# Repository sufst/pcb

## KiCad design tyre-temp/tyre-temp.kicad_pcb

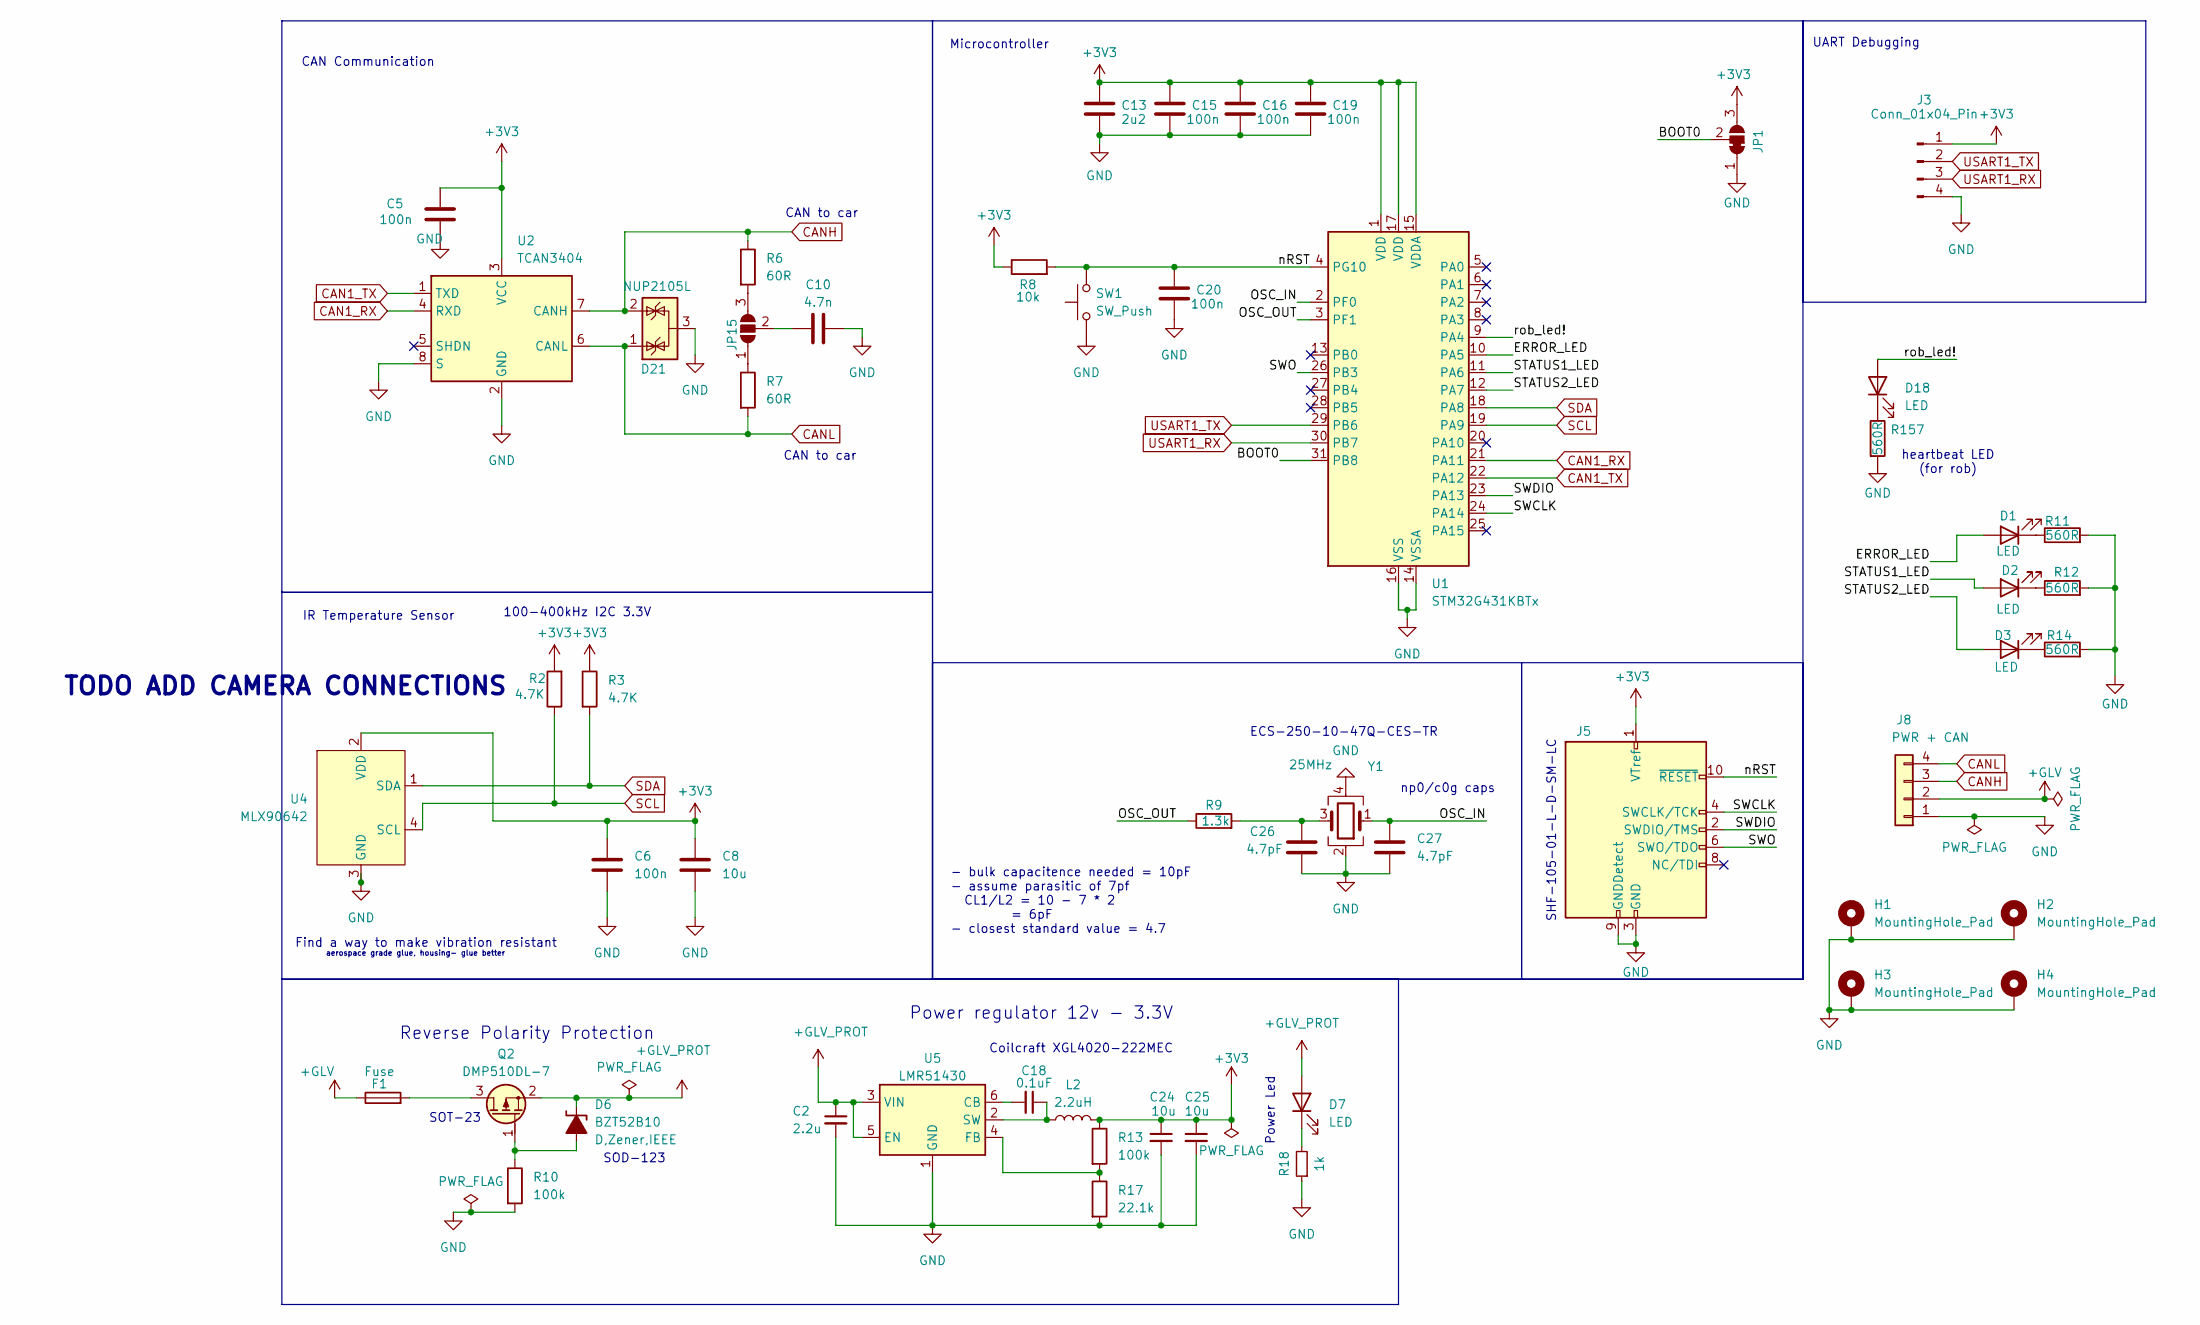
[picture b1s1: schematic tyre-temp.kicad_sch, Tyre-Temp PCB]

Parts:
C2: 2.2u; C_0603_1608Metric_Pad1.08x0.95mm_HandSolder
C5, C6, C15, C16, C19, C20: 100n; C_0603_1608Metric_Pad1.08x0.95mm_HandSolder
C8, C24, C25: 10u; C_0805_2012Metric_Pad1.18x1.45mm_HandSolder
C10: 4.7n; C_0603_1608Metric_Pad1.08x0.95mm_HandSolder
C13: 2u2; C_0603_1608Metric_Pad1.08x0.95mm_HandSolder
C18: 0.1uF; C_0603_1608Metric_Pad1.08x0.95mm_HandSolder
C26, C27: 4.7pF; C_0603_1608Metric_Pad1.08x0.95mm_HandSolder; Mouser Order Number 791-0402N4R7C500CT
D1, D2, D3, D7, D18: LED; LED_0603_1608Metric_Pad1.05x0.95mm_HandSolder
D6: BZT52B10; D_SOD-123; MPN BZT52B10
D21: NUP2105L; SOT-23; Mouser Order Number 863-NUP2105LT1G
F1: Fuse; Fuse_0603_1608Metric_Pad1.05x0.95mm_HandSolder
H1, H2, H3, H4: MountingHole_Pad; MountingHole_3.2mm_M3_ISO7380_Pad_TopBottom
J3: Conn_01x04_Pin; PinHeader_1x04_P2.54mm_Vertical
J5: SHF10501LDSMLC; Mouser Order Number 200-SHF10501LDSMLC
J8: PWR + CAN; Molex_Micro-Fit_3.0_43045-0400_2x02_P3.00mm_Horizontal
JP1: SolderJumper_3_Bridged12; SolderJumper-3_P1.3mm_Bridged2Bar12_RoundedPad1.0x1.5mm
JP15: SolderJumper_3_Open; SolderJumper-3_P1.3mm_Open_RoundedPad1.0x1.5mm
L2: 2.2uH; L_Coilcraft_XAL4020-XXX; MPN XAL4020-222MEC
Q2: DMP510DL-7; SOT-23
R2, R3: 4.7K; R_0603_1608Metric_Pad0.98x0.95mm_HandSolder
R6, R7: 60R; R_0603_1608Metric_Pad0.98x0.95mm_HandSolder
R8: 10k; R_0603_1608Metric_Pad0.98x0.95mm_HandSolder
R9: 1.3k; R_0603_1608Metric_Pad0.98x0.95mm_HandSolder; Mouser Order Number 603-RC0402FR-071K3L
R10, R13: 100k; R_0603_1608Metric_Pad0.98x0.95mm_HandSolder
R11, R12, R14, R157: 560R; R_0603_1608Metric_Pad0.98x0.95mm_HandSolder; Mouser Order Number 603-RC0402FR-07560RL
R17: 22.1k; R_0603_1608Metric_Pad0.98x0.95mm_HandSolder
R18: 1k; R_0603_1608Metric_Pad0.98x0.95mm_HandSolder
SW1: SW_Push; SW_Push_1P1T_NO_CK_KMR2
U1: STM32G431KBTx; LQFP-32_7x7mm_P0.8mm
U2: TCAN3404; TSOT-23-8_HandSoldering
U4: MLX90642
U5: LMR51430; SOT-23-6; MPN LMR51430YDDCR
Y1: 25MHz; Resonator_SMD_ECS_ECX-1247Q_1.6x1.2x0.3mm; Mouser Order Number 520-250-10-47Q-CEST

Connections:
+3V3: C5.1, C6.1, C8.1, C13.2, C15.2, C16.2, C19.2, C24.1, C25.1, J3.1, J5.1 (VTref), JP1.3 (B), L2.2, R2.2, R3.1, R8.1, R13.1, U1.1 (VDD), U1.15 (VDDA), U1.17 (VDD), U2.3 (VCC), U4.2 (VDD)
+GLV: F1.1, J8.2
+GLV_PROT: C2.1, D6.1 (K-), D7.2 (A), Q2.2 (S), U5.3 (VIN), U5.5 (EN)
/BOOT0: JP1.2 (C), U1.31 (PB8)
/ERROR_LED: D1.2 (A), U1.10 (PA5)
/OSC_IN: C27.1, U1.2 (PF0), Y1.1
/OSC_OUT: R9.1, U1.3 (PF1)
/STATUS1_LED: D2.2 (A), U1.11 (PA6)
/STATUS2_LED: D3.2 (A), U1.12 (PA7)
/SWCLK: J5.4 (SWCLK/TCK), U1.24 (PA14)
/SWDIO: J5.2 (SWDIO/TMS), U1.23 (PA13)
/SWO: J5.6 (SWO/TDO), U1.26 (PB3)
/nRST: C20.2, J5.10 (~RESET), R8.2, SW1.2, U1.4 (PG10)
/rob_led!: D18.2 (A), U1.9 (PA4)
CAN1_RX: U1.21 (PA11), U2.4 (RXD)
CAN1_TX: U1.22 (PA12), U2.1 (TXD)
CANH: D21.2 (K), J8.3, R6.1, U2.7 (CANH)
CANL: D21.1 (K), J8.4, R7.2, U2.6 (CANL)
GND: C2.2, C5.2, C6.2, C8.2, C10.2, C13.1, C15.1, C16.1, C19.1, C20.1, C24.2, C25.2, C26.2, C27.2, D21.3 (A), H1.1, H2.1, H3.1, H4.1, J3.4, J5.3 (GND), J5.5 (GND), J5.9 (GNDDetect), J8.1, JP1.1 (A), R10.2, R11.2, R12.2, R14.2, R17.2, R18.1, R157.2, SW1.1, U1.14 (VSSA), U1.16 (VSS), U1.32 (VSS), U2.2 (GND), U2.8 (S), U4.3 (GND), U5.1 (GND), Y1.2, Y1.4
unnamed: C26.1, R9.2, Y1.3
unnamed: D1.1 (K), R11.1
unnamed: D2.1 (K), R12.1
unnamed: D3.1 (K), R14.1
unnamed: D6.2 (A+), Q2.1 (G), R10.1
unnamed: D7.1 (K), R18.2
unnamed: D18.1 (K), R157.1
unnamed: JP15.1 (A), R7.1
unnamed: JP15.3 (B), R6.2
unnamed: C10.1, JP15.2 (C)
unnamed: F1.2, Q2.3 (D)
unnamed: C18.2, U5.6 (CB)
unnamed: R13.2, R17.1, U5.4 (FB)
unnamed: C18.1, L2.1, U5.2 (SW)
SCL: R2.1, U1.19 (PA9), U4.4 (SCL)
SDA: R3.2, U1.18 (PA8), U4.1 (SDA)
USART1_RX: J3.3, U1.30 (PB7)
USART1_TX: J3.2, U1.29 (PB6)

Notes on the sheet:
TODO ADD CAMERA CONNECTIONS
100-400kHz I2C 3.3V
CAN Communication
aerospace grade glue, housing- glue better
Microcontroller
Power regulator 12v - 3.3V
Power Led
CAN to car
Reverse Polarity Protection
Find a way to make vibration resistant
ECS-250-10-47Q-CES-TR
np0/c0g caps
heartbeat LED (for rob)
- bulk capacitence needed = 10pF - assume parasitic of 7pf CL1/L2 = 10 - 7 * 2 = 6pF - closest standard value = 4.7
SHF-105-01-L-D-SM-LC
SOD-123
Coilcraft XGL4020-222MEC
SOT-23
UART Debugging
IR Temperature Sensor

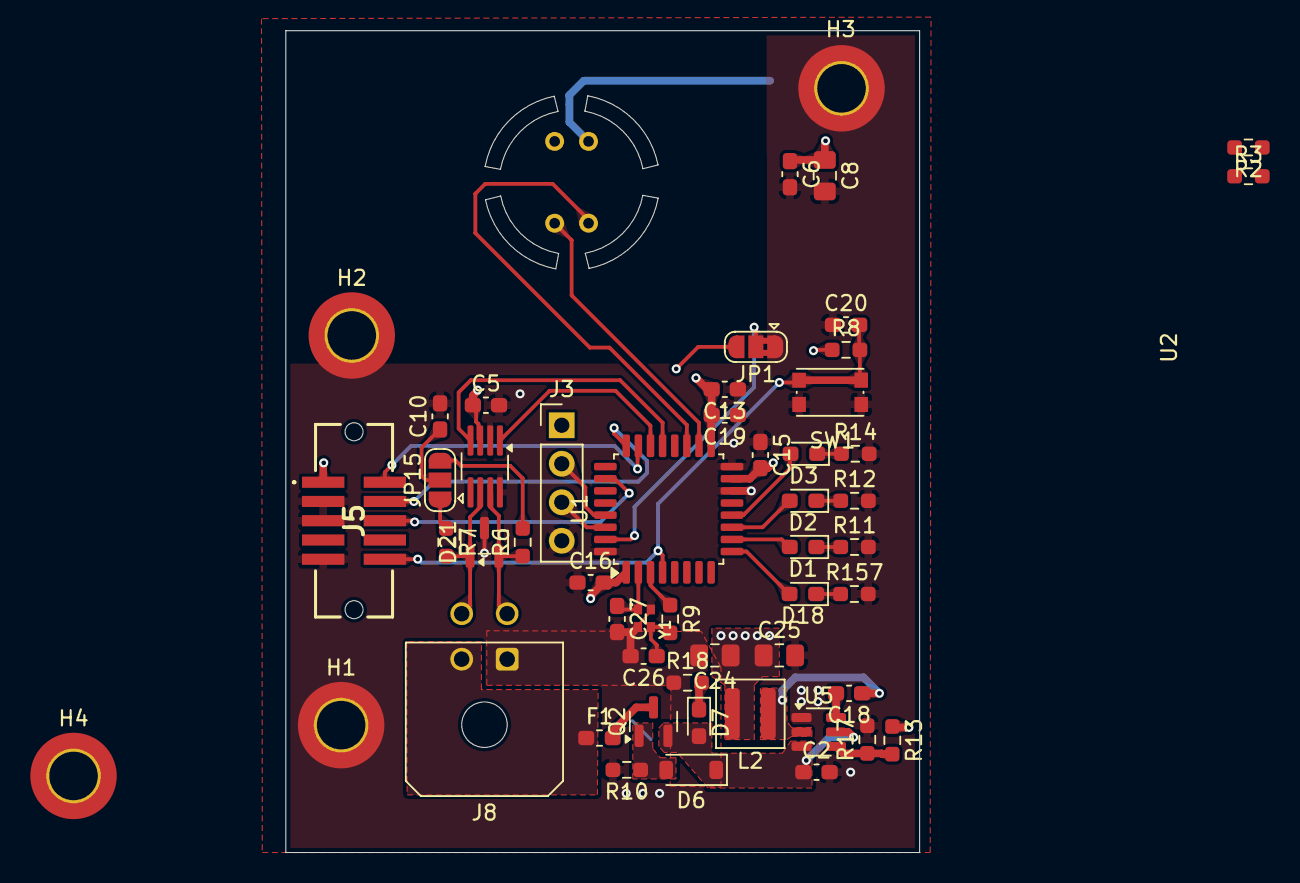
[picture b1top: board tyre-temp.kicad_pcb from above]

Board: 4 copper layers, 41.8 x 54.2 mm, 54 parts (1 on the bottom side), 37 nets.

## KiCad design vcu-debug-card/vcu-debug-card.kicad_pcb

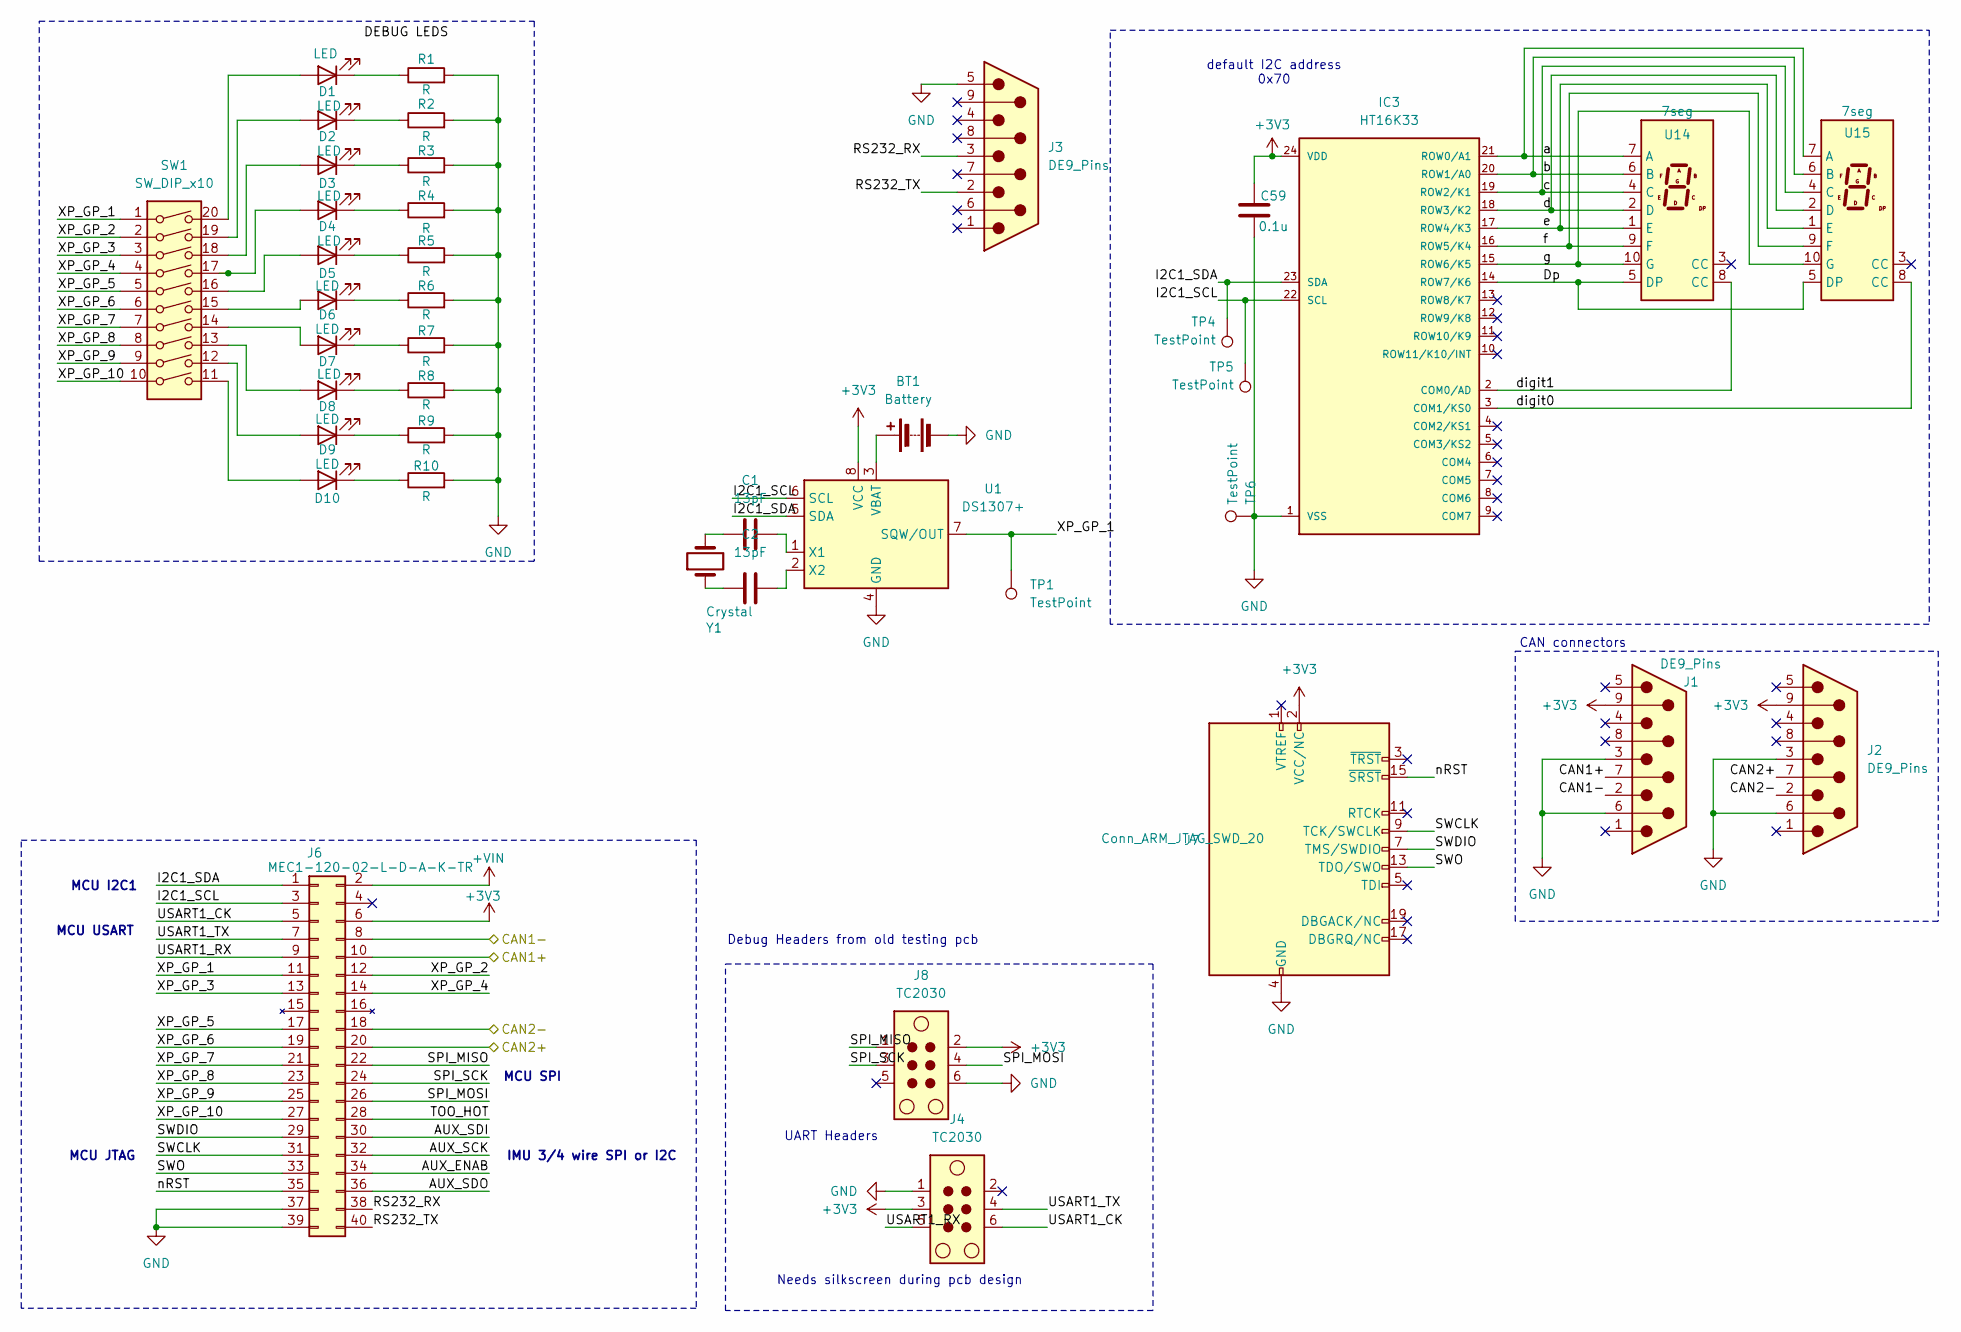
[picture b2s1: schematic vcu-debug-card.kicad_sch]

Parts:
BT1: Battery; BatteryHolder_Multicomp_BC-2001_1x2032; MPN 2898
C1, C2: 13pF; C_0402_1005Metric_Pad0.74x0.62mm_HandSolder; MPN 04023K130FBSTR
C59: 0.1u; C_0805_2012Metric_Pad1.18x1.45mm_HandSolder
D1, D2, D3, D4, D5, D6, D7, D8, D9, D10: LED; LED_0805_2012Metric_Pad1.15x1.40mm_HandSolder
IC3: HT16K33
J1, J2, J3: DE9_Pins; AMPHENOL_D09P71S6GA12LF
J4, J8: TC2030; Tag-Connect_TC2030-IDC-NL_2x03_P1.27mm_Vertical
J6: MEC1-120-02-L-D-A-K-TR; Edge Connector; Mouser Order Number 200-MEC112002LDAKTR
J7: Conn_ARM_JTAG_SWD_20; IDC-Header_2x10_P2.54mm_Vertical
R1, R2, R3, R4, R5, R6, R7, R8, R9, R10: R; R_0603_1608Metric_Pad0.98x0.95mm_HandSolder
SW1: SW_DIP_x10; DipSwitch; MPN NDS10V
TP1, TP4, TP5, TP6: TestPoint; TestPoint_THTPad_D2.5mm_Drill1.2mm
U1: DS1307+; DIP-8_W7.62mm; MPN DS1343E-33+
U14, U15: 7seg; Vishay TDSG5160-MN 7-Segment Display; MPN TDSG5160-MN
Y1: Crystal; CC7V-T1A-32.768kHz-12.5pF-20PPM-TA-QC; MPN CC7V-T1A-32.768kHz-12.5pF-20PPM-TA-QC

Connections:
+3V3: C59.1, IC3.24 (VDD), J1.9, J2.9, J4.3, J6.6, J7.2 (VCC/NC), J8.2, U1.8 (VCC)
+VIN: J6.2
/<NO NET>: J1.2, J6.8
/AUX_ENAB: J6.34
/AUX_SCK: J6.32
/AUX_SDI: J6.30
/AUX_SDO: J6.36
/CAN1+: J1.7, J6.10
/CAN2+: J2.7, J6.20
/CAN2-: J2.2, J6.18
/Dp: IC3.14 (ROW7/K6), U14.5 (DP), U15.5 (DP)
/I2C1_SCL: IC3.22 (SCL), J6.3, TP5.1, U1.6 (SCL)
/I2C1_SDA: IC3.23 (SDA), J6.1, TP4.1, U1.5 (SDA)
/RS232_RX: J3.3, J6.38
/RS232_TX: J3.2, J6.40
/SPI_MISO: J6.22, J8.1
/SPI_MOSI: J6.26, J8.4
/SPI_SCK: J6.24, J8.3
/SWCLK: J6.31, J7.9 (TCK/SWCLK)
/SWDIO: J6.29, J7.7 (TMS/SWDIO)
/SWO: J6.33, J7.13 (TDO/SWO)
/TOO_HOT: J6.28
/USART1_CK: J4.6, J6.5
/USART1_RX: J4.5, J6.9
/USART1_TX: J4.4, J6.7
/XP_GP_1: J6.11, SW1.1, TP1.1, U1.7 (SQW/OUT)
/XP_GP_2: J6.12, SW1.2
/XP_GP_3: J6.13, SW1.3
/XP_GP_4: J6.14, SW1.4
/XP_GP_5: J6.17, SW1.5
/XP_GP_6: J6.19, SW1.6
/XP_GP_7: J6.21, SW1.7
/XP_GP_8: J6.23, SW1.8
/XP_GP_9: J6.25, SW1.9
/XP_GP_10: J6.27, SW1.10
/a: IC3.19 (ROW2/K1), IC3.20 (ROW1/A0), IC3.21 (ROW0/A1), U14.4 (C), U14.6 (B), U14.7 (A), U15.4 (C), U15.6 (B), U15.7 (A)
/d: IC3.18 (ROW3/K2), U14.2 (D), U15.2 (D)
/digit0: IC3.3 (COM1/KS0), U15.8 (CC)
/digit1: IC3.2 (COM0/AD), U14.8 (CC)
/e: IC3.17 (ROW4/K3), U14.1 (E), U15.1 (E)
/f: IC3.16 (ROW5/K4), U14.9 (F), U15.9 (F)
/g: IC3.15 (ROW6/K5), U14.10 (G), U15.10 (G)
/nRST: J6.35, J7.15 (~SRST)
GND: BT1.2 (-), C59.2, IC3.1 (VSS), J1.3, J1.6, J2.3, J2.6, J3.5, J4.1, J6.37, J6.39, J7.4 (GND), J7.6 (GND), J7.8 (GND), J7.10 (GND), J7.12 (GND), J7.14 (GND), J7.16 (GND), J7.18 (GND), J7.20 (GND), J8.6, R1.2, R2.2, R3.2, R4.2, R5.2, R6.2, R7.2, R8.2, R9.2, R10.2, TP6.1, U1.4 (GND)
unnamed: BT1.1 (+), U1.3 (VBAT)
unnamed: C1.1, Y1.2
unnamed: C2.1, Y1.1
unnamed: D1.2 (A), SW1.20
unnamed: D1.1 (K), R1.1
unnamed: D2.2 (A), SW1.19
unnamed: D2.1 (K), R2.1
unnamed: D3.2 (A), SW1.18
unnamed: D3.1 (K), R3.1
unnamed: D4.2 (A), SW1.17
unnamed: D4.1 (K), R4.1
unnamed: D5.2 (A), SW1.16
unnamed: D5.1 (K), R5.1
unnamed: D6.2 (A), SW1.15
unnamed: D6.1 (K), R6.1
unnamed: D7.2 (A), SW1.14
unnamed: D7.1 (K), R7.1
unnamed: D8.2 (A), SW1.13
unnamed: D8.1 (K), R8.1
unnamed: D9.2 (A), SW1.12
unnamed: D9.1 (K), R9.1
unnamed: D10.2 (A), SW1.11
unnamed: D10.1 (K), R10.1
unnamed: C1.2, U1.1 (X1)
unnamed: C2.2, U1.2 (X2)

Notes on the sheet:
MCU SPI
Debug Headers from old testing pcb
Needs silkscreen during pcb design
UART Headers
CAN connectors
MCU I2C1
IMU 3/4 wire SPI or I2C
MCU JTAG
default I2C address 0x70
MCU USART

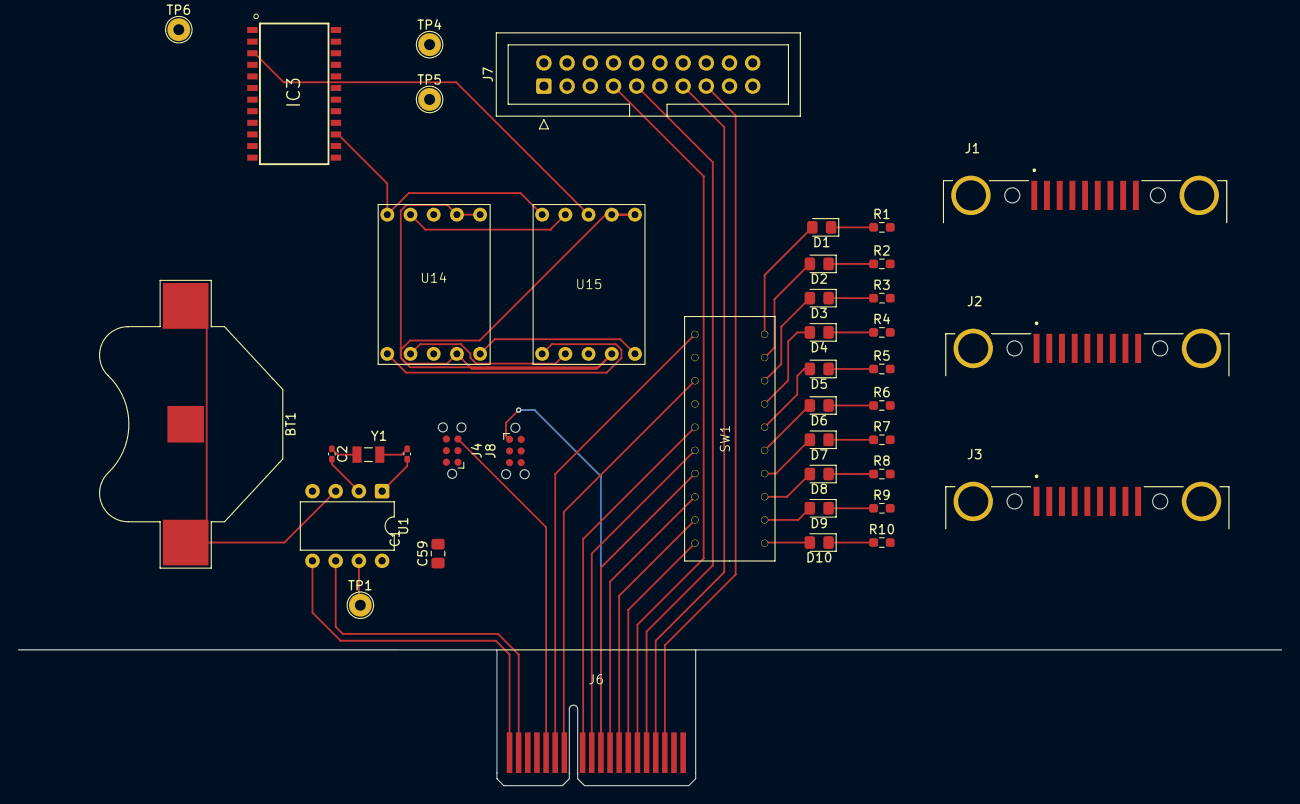
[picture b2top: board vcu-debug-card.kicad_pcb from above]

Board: 4 copper layers, 41 parts (0 on the bottom side), 63 nets.

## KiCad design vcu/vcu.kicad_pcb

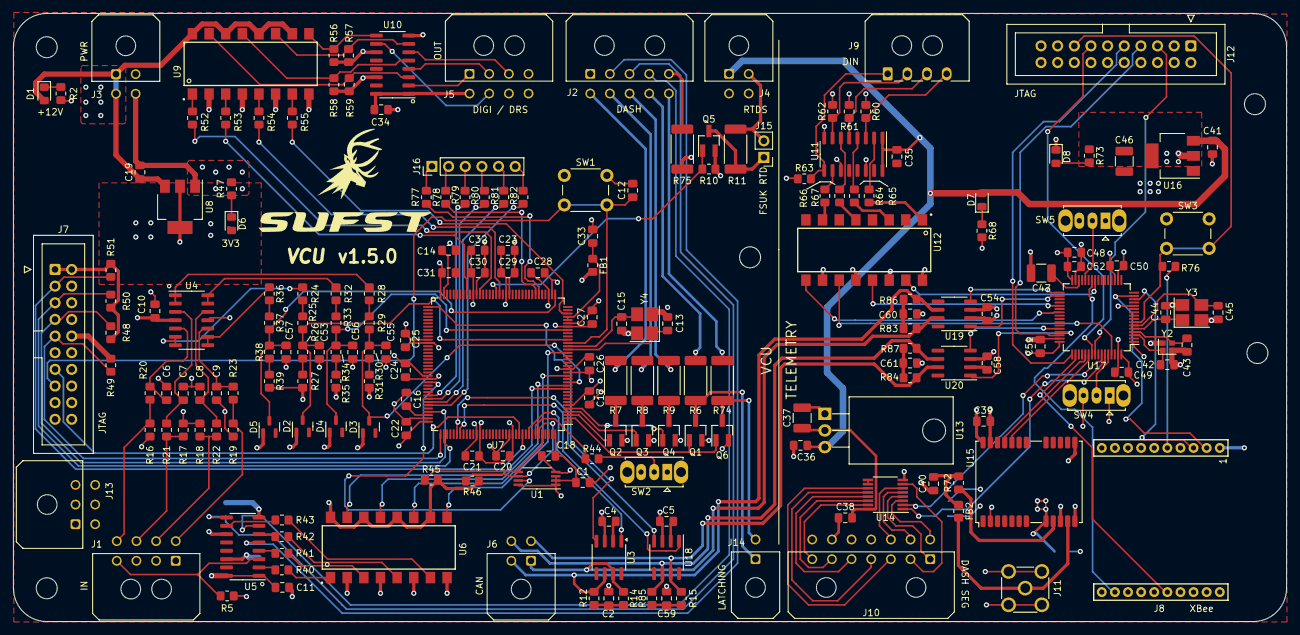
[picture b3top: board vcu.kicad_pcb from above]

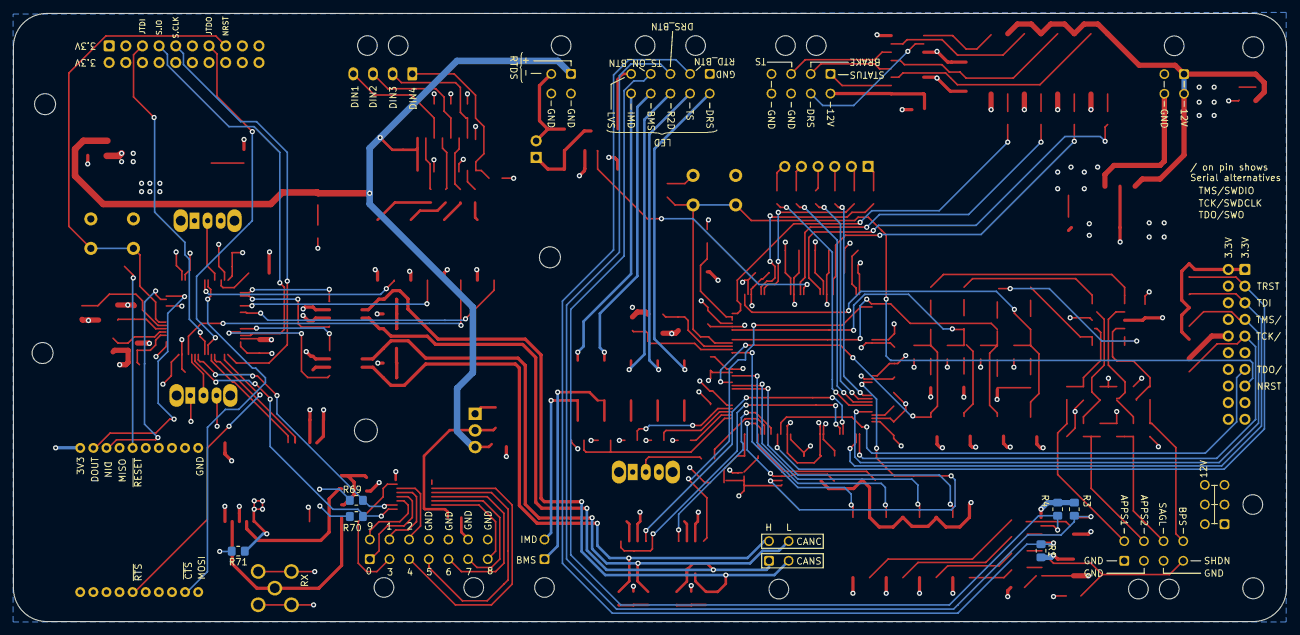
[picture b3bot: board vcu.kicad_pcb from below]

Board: 4 copper layers, 194.3 x 92.8 mm, 210 parts (6 on the bottom side), 177 nets.

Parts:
C1, C4, C5, C6, C7, C8, C9, C10, C11, C12, C17, C18, C19, C20, C21, C22, C24, C25, C26, C27, C28, C29, C30, C33, C34, C35, C36, C38, C54, C58: 100n; C_0805_2012Metric_Pad1.18x1.45mm_HandSolder
C2, C59, C60, C61: 4.7n; C_0805_2012Metric_Pad1.18x1.45mm_HandSolder
C13, C15: 4.3p; C_0805_2012Metric_Pad1.18x1.45mm_HandSolder
C14, C16: 2.2u; C_0805_2012Metric_Pad1.18x1.45mm_HandSolder
C23: 10u; C_0805_2012Metric_Pad1.18x1.45mm_HandSolder
C31: 4.7u; C_0805_2012Metric_Pad1.18x1.45mm_HandSolder
C32: 1u; C_0805_2012Metric_Pad1.18x1.45mm_HandSolder
C37: 10u; C_1210_3225Metric_Pad1.33x2.70mm_HandSolder
C39, C41, C49, C50, C51, C52: 100nF; C_0805_2012Metric_Pad1.18x1.45mm_HandSolder
C40: 47pF; C_0805_2012Metric_Pad1.18x1.45mm_HandSolder
C42, C43: 4p3; C_0805_2012Metric_Pad1.18x1.45mm_HandSolder
C44, C45: 20pF; C_0805_2012Metric_Pad1.18x1.45mm_HandSolder
C46: 10uF; C_1210_3225Metric_Pad1.33x2.70mm_HandSolder
C47: 4u7; C_1210_3225Metric_Pad1.33x2.70mm_HandSolder
C48: 4.7uF; C_0805_2012Metric_Pad1.18x1.45mm_HandSolder
C53, C55, C56, C57: 1n; C_0805_2012Metric_Pad1.18x1.45mm_HandSolder
D1, D6, D7, D8: LED; LED_0805_2012Metric_Pad1.15x1.40mm_HandSolder
D2, D3, D4, D5: BZX84-C3V3; SOT-23
FB1, FB2: 120; R_0805_2012Metric_Pad1.20x1.40mm_HandSolder
H1, H2, H3, H5, H6: M3; MountingHole_3.2mm_M3
J1: IN; Molex_Micro-Fit_3.0_43045-0800_2x04_P3.00mm_Horizontal
J2: DASH CONTROL; Molex_Micro-Fit_3.0_43045-1000_2x05_P3.00mm_Horizontal
J3: PWR; Molex_Micro-Fit_3.0_43045-0400_2x02_P3.00mm_Horizontal
J4: RTDS; Molex_Micro-Fit_3.0_43045-0400_2x02_P3.00mm_Horizontal
J5: OUT; Molex_Micro-Fit_3.0_43045-0800_2x04_P3.00mm_Horizontal
J6: CAN; Molex_Micro-Fit_3.0_43045-0400_2x02_P3.00mm_Horizontal
J7, J12: Conn_ARM_JTAG_SWD_20; IDC-Header_2x10_P2.54mm_Vertical
J8: XBee; XBEE
J9: MCU_DIN; Molex_Micro-Fit_3.0_43650-0400_1x04_P3.00mm_Horizontal
J10: Dash 7 Segment; Molex_Micro-Fit_3.0_43045-1400_2x07_P3.00mm_Horizontal
J11: Conn_Coaxial; SMA_Molex_73251-2200_Horizontal
J13: DASH 12V; Molex_Micro-Fit_3.0_43045-0600_2x03_P3.00mm_Horizontal
J14: BMS+IMD LATCHING; Molex_Micro-Fit_3.0_43045-0200_2x01_P3.00mm_Horizontal
J15: FSUK_RTD; PinHeader_1x02_P2.54mm_Vertical
J16: Spare pins; PinHeader_1x06_P2.54mm_Vertical
Q1, Q2, Q3, Q4, Q5, Q6: FDN359BN; SOT-23_Handsoldering
R1, R3, R4, R5, R44, R45, R46, R48, R49, R50, R51, R56, R57, R58, R59, R60, R61, R62, R63: 10k; R_0805_2012Metric_Pad1.20x1.40mm_HandSolder
R2, R68: 3.3k; R_0805_2012Metric_Pad1.20x1.40mm_HandSolder
R6, R7, R8, R9, R11, R74, R75: 1k; R_2512_6332Metric_Pad1.40x3.35mm_HandSolder
R10: 3k3; R_0805_2012Metric_Pad1.20x1.40mm_HandSolder
R12, R14, R15, R83, R84, R85, R86, R87: 60R; R_0805_2012Metric_Pad1.20x1.40mm_HandSolder
R16, R17, R18, R19: 100k; R_0805_2012Metric_Pad1.20x1.40mm_HandSolder
R20, R21, R22, R23, R40, R41, R42, R43, R64, R65, R66, R67: 1k; R_0805_2012Metric_Pad1.20x1.40mm_HandSolder
R24, R28, R32, R36: 75k; R_0805_2012Metric_Pad1.20x1.40mm_HandSolder
R25, R26, R29, R30, R33, R34, R37, R38: 5.6k; R_0805_2012Metric_Pad1.20x1.40mm_HandSolder
R27, R31, R35, R39: 1.8k; R_0805_2012Metric_Pad1.20x1.40mm_HandSolder
R47, R73: 1k5; R_0805_2012Metric_Pad1.20x1.40mm_HandSolder
R52, R53, R54, R55: 220; R_0805_2012Metric_Pad1.20x1.40mm_HandSolder
R69, R70: 4k7; R_0805_2012Metric_Pad1.20x1.40mm_HandSolder
R71: DNP; R_0805_2012Metric_Pad1.20x1.40mm_HandSolder
R72: 33; R_0805_2012Metric_Pad1.20x1.40mm_HandSolder
R76: 0; R_0805_2012Metric_Pad1.20x1.40mm_HandSolder
R77, R78, R79, R80, R81, R82: 100; R_0805_2012Metric_Pad1.20x1.40mm_HandSolder
SW1, SW3: SW_Push; SW_PUSH_6mm
SW2, SW4, SW5: SW_SPDT; SW_Slide_1P2T_CK_OS102011MS2Q
U1: M24256-DRD; TSSOP-8_4.4x3mm_P0.65mm
U3, U18, U19, U20: MAX3051ESA+; SOIC-8_3.9x4.9mm_P1.27mm
U4: TLV274; SOIC-14_3.9x8.7mm_P1.27mm
U5, U10, U11: HCF4010; SOIC-16_3.9x9.9mm_P1.27mm
U6, U9, U12: ILQ615-4X009T; SOIC254P1005X380-16N
U7: STM32F746ZGT6; LQFP-144_20x20mm_P0.5mm
U8, U16: LD1117S33TR_SOT223; SOT-223-3_TabPin2
U13: LD1117V33; TO-220-3_Horizontal_TabDown
U14: MAX6958BAEE+T; QSOP-16_3.9x4.9mm_P0.635mm
U15: NEO-M9N; ublox_NEO
U17: STM32F446RETx; LQFP-64_10x10mm_P0.5mm
Y2: 32MHz; Crystal_SMD_2016-4Pin_2.0x1.6mm
Y3, Y4: 8MHz; Crystal_SMD_3225-4Pin_3.2x2.5mm_HandSoldering

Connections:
+3.3V: C1.1, C4.2, C5.2, C17.1, C18.1, C20.1, C21.1, C22.1, C23.1, C24.1, C25.1, C26.1, C27.1, C28.1, C29.1, C30.1, C31.1, C32.1, D6.2 (A), FB1.2, J7.1 (VTREF), J7.2 (VCC/NC), R45.2, R46.1, R48.2, R50.2, R51.2, SW2.3 (C), U1.1 (E0), U1.2 (E1), U1.3 (E2), U1.8 (VCC), U3.3 (VDD), U6.10, U6.12, U6.14, U6.16, U7.6 (VBAT), U7.17 (VDD), U7.30 (VDD), U7.39 (VDD), U7.52 (VDD), U7.62 (VDD), U7.72 (VDD), U7.84 (VDD), U7.95 (VDDUSB), U7.108 (VDD), U7.121 (VDD), U7.131 (VDD), U7.144 (VDD), U8.2 (VO), U18.3 (VDD)
+3.3VA: C33.1, FB1.1, U7.32 (VREF+), U7.33 (VDDA)
+3.3VT: C39.2, C46.2, C48.1, C49.1, C50.1, C51.1, C52.1, C54.2, C58.2, J8.1, J12.1 (VTREF), J12.2 (VCC/NC), R69.1, R70.1, R71.1, R73.1, SW4.3 (C), SW5.1 (A), U12.10, U12.12, U12.14, U12.16, U15.2 (D_SEL), U15.8 (~RESET), U15.23 (VCC), U16.2 (VO), U17.1 (VBAT), U17.19 (VDD), U17.32 (VDD), U17.48 (VDD), U17.64 (VDD), U19.3 (VDD), U20.3 (VDD)
+12V: C10.2, C11.2, C19.1, C34.2, C35.2, C36.2, C41.2, D1.2 (A), D7.2 (A), J3.1, J3.3, J4.1, J5.5, J13.1, J13.2, J13.3, J13.4, J13.5, J13.6, U4.4 (V+), U5.1 (VCC), U5.16 (VDD), U8.3 (VI), U9.10, U9.12, U9.14, U9.16, U10.1 (VCC), U10.16 (VDD), U11.1 (VCC), U11.16 (VDD), U13.3 (VI), U16.3 (VI)
/APPS_1_IN: J1.5, R19.1, R23.1
/APPS_2_IN: J1.6, R18.1, R22.1
/BMS_LED: J2.9, R6.1
/BPS_IN: J1.8, R16.1, R20.1
/BRAKE_PRESSED: J5.2, U10.4 (Bout)
/CAN_C_H: J6.3, R15.2, R84.2, U18.7 (CANH), U20.7 (CANH)
/CAN_C_L: J6.4, R85.1, R87.1, U18.6 (CANL), U20.6 (CANL)
/CAN_S_H: J6.1, R14.2, R83.2, U3.7 (CANH), U19.7 (CANH)
/CAN_S_L: J6.2, R12.1, R86.1, U3.6 (CANL), U19.6 (CANL)
/DRS_BTN: J2.3, R3.1, U5.9 (Din)
/DRS_LED: J2.6, R7.1
/DRS_LED_ON: Q2.1 (G), U7.3 (PE4)
/DRS_PWM: J5.6, U10.10 (Dout)
/EEPROM_SCL: R46.2, U1.6 (SCL), U7.139 (PB8)
/EEPROM_SDA: R45.1, U1.5 (SDA), U7.140 (PB9)
/EEPROM_WC: U1.7 (WC), U7.96 (PC6)
/IMD_LED: J2.10, R74.1
/Input Shift/APPS_1_OUT: C57.2, D5.3 (K), R37.2, R38.1, U7.37 (PA3)
/Input Shift/APPS_2_OUT: C56.2, D4.3 (K), R33.2, R34.1, U7.29 (PC3)
/Input Shift/BPS_OUT: C53.2, D2.3 (K), R25.2, R26.1, U7.26 (PC0)
/Input Shift/DOUT_1: U6.15, U7.11 (PF1)
/Input Shift/DOUT_2: U6.13, U7.12 (PF2)
/Input Shift/DOUT_3: U6.11, U7.15 (PF5)
/Input Shift/DOUT_4: U6.9, U7.22 (PF10)
/Input Shift/SAGL_OUT: C55.2, D3.3 (K), R29.2, R30.1, U7.13 (PF3)
/LVS_LED: J2.5, R75.1
/Output Level Shifting/DIN_1: R52.1, U7.60 (PE9)
/Output Level Shifting/DIN_2: R53.1, U7.64 (PE11)
/Output Level Shifting/DIN_3: R54.1, U7.54 (PF14)
/Output Level Shifting/DIN_4: R55.1, U7.34 (PA0)
/R2D_BTN: J2.2, R1.1, U5.5 (Bin)
/R2D_LED: J2.8, R9.1
/R2D_LED_ON: Q4.1 (G), U7.5 (PE6)
/R2D_SIREN_ON: Q5.1 (G), R10.2, U7.55 (PF15)
/RTDS-: J4.2, J15.2, R11.2
/SAGL_IN: J1.7, R17.1, R21.1
/SHDN_STATE: J1.4, R5.1, U5.3 (Ain)
/STATUS: J5.1, U10.2 (Aout)
/STM32-F746ZG/BOOT0: R44.2, U7.138 (BOOT0)
/STM32-F746ZG/CAN1_RX: U7.114 (PD0), U18.4 (RXD)
/STM32-F746ZG/CAN1_TX: U7.115 (PD1), U18.1 (TXD)
/STM32-F746ZG/CAN2_RX: U3.4 (RXD), U7.73 (PB12)
/STM32-F746ZG/CAN2_TX: U3.1 (TXD), U7.136 (PB6)
/STM32-F746ZG/NRST: C12.1, J7.15 (~SRST), SW1.2, U7.25 (NRST)
/STM32-F746ZG/PWR_LED_K: D6.1 (K), R47.1
/STM32-F746ZG/SW_BOOT0: R44.1, SW2.2 (B)
/STM32-F746ZG/TCK/SWDCLK: J7.9 (TCK/SWCLK), R49.2, U7.109 (PA14)
/STM32-F746ZG/TDI: J7.5 (TDI), R50.1, U7.110 (PA15)
/STM32-F746ZG/TDO/SWO: J7.13 (TDO/SWO), U7.133 (PB3)
/STM32-F746ZG/TMS/SWDIO: J7.7 (TMS/SWDIO), R48.1, U7.105 (PA13)
/STM32-F746ZG/TRST: J7.3 (~TRST), R51.1, U7.134 (PB4)
/TS_ON: J5.3, U10.6 (Cout)
/TS_ON_BTN: J2.4, R4.1, U5.7 (Cin)
/TS_ON_LED: J2.7, R8.1
/TS_ON_LED_ON: Q3.1 (G), U7.4 (PE5)
/Telemetry/3V3_LED: C37.1, C38.2, U13.2 (VO), U14.16 (V+)
/Telemetry/CAN1_RX: U17.44 (PA11), U20.4 (RXD)
/Telemetry/CAN1_TX: U17.45 (PA12), U20.1 (TXD)
/Telemetry/CAN2_RX: U17.33 (PB12), U19.4 (RXD)
/Telemetry/CAN2_TX: U17.34 (PB13), U19.1 (TXD)
/Telemetry/GPS/GPS_RX: U15.21 (RXD/SPI_MOSI), U17.53 (PC12)
/Telemetry/GPS/GPS_TX: U15.20 (TXD/SPI_MISO), U17.54 (PD2)
/Telemetry/SEG0: J10.1, U14.4 (DIG0/SEG0)
/Telemetry/SEG1: J10.9, U14.5 (DIG1/SEG1)
/Telemetry/SEG2: J10.10, U14.6 (DIG2/SEG2)
/Telemetry/SEG3: J10.2, U14.7 (DIG3/SEG3)
/Telemetry/SEG4: J10.3, U14.11 (SEG4)
/Telemetry/SEG5: J10.4, U14.12 (SEG5)
/Telemetry/SEG6: J10.5, U14.13 (SEG6)
/Telemetry/SEG7: J10.6, U14.14 (SEG7)
/Telemetry/SEG8: J10.7, U14.15 (SEG8)
/Telemetry/SEG9: J10.8, U14.3 (SEG9)
/Telemetry/XBee Module/DIN/`CONFIG/DIO14: J8.3, U17.14 (PA0)
/Telemetry/XBee Module/DOUT/DIO13: J8.2, U17.15 (PA1)
/Telemetry/XBee Module/~CTS: J8.12, U17.26 (PB0)
/Telemetry/XBee Module/~RESET: J8.5, R76.2
/Telemetry/XBee Module/~RTS: J8.16, U17.50 (PA15)
/Telemetry/telemetry input shift/DIN_1: J9.4, R60.2, U11.3 (Ain)
/Telemetry/telemetry input shift/DIN_2: J9.3, R61.2, U11.5 (Bin)
/Telemetry/telemetry input shift/DIN_3: J9.2, R62.2, U11.7 (Cin)
/Telemetry/telemetry input shift/DIN_4: J9.1, R63.2, U11.9 (Din)
/Telemetry/telemetry input shift/DOUT_1: U12.15, U17.25 (PC5)
/Telemetry/telemetry input shift/DOUT_2: U12.13, U17.37 (PC6)
/Telemetry/telemetry input shift/DOUT_3: U12.11, U17.61 (PB8)
/Telemetry/telemetry input shift/DOUT_4: U12.9, U17.39 (PC8)
/Telemetry/telemetrymcu/BOOT0: SW4.2 (B), U17.60 (BOOT0)
/Telemetry/telemetrymcu/BOOT1: SW5.2 (B), U17.28 (PB2)
/Telemetry/telemetrymcu/I2C1_SCL: R69.2, U14.2 (SCL), U17.58 (PB6)
/Telemetry/telemetrymcu/I2C1_SDA: R70.2, U14.1 (SDA), U17.59 (PB7)
/Telemetry/telemetrymcu/OSC_IN: C44.2, U17.5 (PH0), Y3.1
/Telemetry/telemetrymcu/OSC_OUT: C45.2, U17.6 (PH1), Y3.3
/Telemetry/telemetrymcu/PWR_LED: D8.2 (A), R73.2
/VC_LEDS_ON: Q1.1 (G), Q6.1 (G), U7.2 (PE3)
GND: C1.2, C2.2, C4.1, C5.1, C6.1, C7.1, C8.1, C9.1, C10.1, C11.1, C12.2, C13.2, C14.1, C15.2, C16.1, C17.2, C18.2, C19.2, C20.2, C21.2, C22.2, C23.2, C24.2, C25.2, C26.2, C27.2, C28.2, C29.2, C30.2, C31.2, C32.2, C33.2, C34.1, C35.1, C36.1, C37.2, C38.1, C39.1, C40.1, C41.1, C42.1, C43.1, C44.1, C45.1, C46.1, C47.2, C48.2, C49.2, C50.2, C51.2, C52.2, C53.1, C54.1, C55.1, C56.1, C57.1, C58.1, C59.2, C60.2, C61.2, D2.1 (A), D3.1 (A), D4.1 (A), D5.1 (A), D8.1 (K), J1.1, J1.2, J1.3, J2.1, J3.2, J3.4, J4.3, J4.4, J5.4, J5.7, J5.8, J7.4 (GND), J7.6 (GND), J7.8 (GND), J7.10 (GND), J7.11 (RTCK), J7.12 (GND), J7.14 (GND), J7.16 (GND), J7.18 (GND), J7.20 (GND), J8.10, J10.11, J10.12, J10.13, J10.14, J11.2 (Ext), J12.4 (GND), J12.6 (GND), J12.8 (GND), J12.10 (GND), J12.11 (RTCK), J12.12 (GND), J12.14 (GND), J12.16 (GND), J12.18 (GND), J12.20 (GND), Q1.2 (S), Q2.2 (S), Q3.2 (S), Q4.2 (S), Q5.2 (S), Q6.2 (S), R1.2, R2.2, R3.2, R4.2, R5.2, R10.1, R16.2, R17.2, R18.2, R19.2, R27.2, R31.2, R35.2, R39.2, R47.2, R49.1, R56.2, R57.2, R58.2, R59.2, R60.1, R61.1, R62.1, R63.1, R68.2, R71.2, R75.2, SW1.1, SW2.1 (A), SW3.1, SW4.1 (A), SW5.3 (C), U1.4 (VSS), U3.2 (GND), U3.8 (RS), U4.11 (V-), U5.8 (VSS), U5.11 (Ein), U5.14 (Fin), U6.2, U6.4, U6.6, U6.8, U7.16 (VSS), U7.31 (VSSA), U7.38 (VSS), U7.51 (VSS), U7.61 (VSS), U7.83 (VSS), U7.94 (VSS), U7.107 (VSS), U7.120 (VSS), U7.130 (VSS), U8.1 (GND), U9.2, U9.4, U9.6, U9.8, U10.8 (VSS), U10.11 (Ein), U10.14 (Fin), U11.8 (VSS), U11.11 (Ein), U11.14 (Fin), U12.2, U12.4, U12.6, U12.8, U13.1 (GND), U14.8 (GND), U15.10 (GND), U15.12 (GND), U15.13 (GND), U15.24 (GND), U16.1 (GND), U17.12 (VSSA), U17.18 (VSS), U17.31 (VSS), U17.47 (VSS), U17.63 (VSS), U18.2 (GND), U18.8 (RS), U19.2 (GND), U19.8 (RS), U20.2 (GND), U20.8 (RS), Y2.2, Y2.4, Y3.2, Y3.4, Y4.2, Y4.4
JTDI: J12.5 (TDI), U17.56 (PB4)
JTDO: J12.13 (TDO/SWO), U17.55 (PB3)
NRST: J12.15 (~SRST), R76.1, SW3.2, U17.7 (NRST)
unnamed: C2.1, R12.2, R14.1
unnamed: C40.2, FB2.1, R72.2
unnamed: C59.1, R15.1, R85.2
unnamed: C60.1, R83.1, R86.2
unnamed: C61.1, R84.1, R87.2
unnamed: D1.1 (K), R2.1
unnamed: D7.1 (K), R68.1
unnamed: FB2.2, J11.1 (In), U15.11 (RF_IN)
unnamed: J14.1, Q1.3 (D), R6.2
unnamed: J14.2, Q6.3 (D), R74.2
unnamed: J15.1, Q5.3 (D), R11.1
unnamed: J16.1, R77.2
unnamed: J16.2, R78.2
unnamed: J16.3, R79.2
unnamed: J16.4, R80.2
unnamed: J16.5, R81.2
unnamed: J16.6, R82.2
unnamed: Q2.3 (D), R7.2
unnamed: Q3.3 (D), R8.2
unnamed: Q4.3 (D), R9.2
unnamed: R24.2, R25.1
unnamed: R26.2, R27.1
unnamed: R28.2, R29.1
unnamed: R30.2, R31.1
unnamed: R32.2, R33.1
unnamed: R34.2, R35.1
unnamed: R36.2, R37.1
unnamed: R38.2, R39.1
unnamed: R40.2, U6.1
unnamed: R41.2, U6.3
unnamed: R42.2, U6.5
unnamed: R43.2, U6.7
unnamed: R52.2, U9.1
unnamed: R53.2, U9.3
unnamed: R54.2, U9.5
unnamed: R55.2, U9.7
unnamed: R64.2, U12.1
unnamed: R65.2, U12.3
unnamed: R66.2, U12.5
unnamed: R67.2, U12.7
unnamed: C7.2, R21.2, U4.3 (+)
unnamed: R28.1, U4.1, U4.2 (-)
unnamed: C6.2, R20.2, U4.5 (+)
unnamed: R24.1, U4.6 (-), U4.7
unnamed: C9.2, R23.2, U4.10 (+)
unnamed: R36.1, U4.8, U4.9 (-)
unnamed: C8.2, R22.2, U4.12 (+)
unnamed: R32.1, U4.13 (-), U4.14
unnamed: R40.1, U5.2 (Aout)
unnamed: R41.1, U5.4 (Bout)
unnamed: R42.1, U5.6 (Cout)
unnamed: R43.1, U5.10 (Dout)
unnamed: R77.1, U7.42 (PA6)
unnamed: R78.1, U7.43 (PA7)
unnamed: R79.1, U7.100 (PA8)
unnamed: R80.1, U7.101 (PA9)
unnamed: R81.1, U7.102 (PA10)
unnamed: R82.1, U7.103 (PA11)
unnamed: C13.1, U7.23 (PH0), Y4.1
unnamed: C15.1, U7.24 (PH1), Y4.3
unnamed: C14.2, U7.71 (VCAP_1)
unnamed: C16.2, U7.106 (VCAP_2)
unnamed: R59.1, U9.15, U10.3 (Ain)
unnamed: R58.1, U9.13, U10.5 (Bin)
unnamed: R57.1, U9.11, U10.7 (Cin)
unnamed: R56.1, U9.9, U10.9 (Din)
unnamed: R64.1, U11.2 (Aout)
unnamed: R65.1, U11.4 (Bout)
unnamed: R66.1, U11.6 (Cout)
unnamed: R67.1, U11.10 (Dout)
unnamed: R72.1, U15.9 (VCC_RF)
unnamed: C42.2, U17.3 (PC14), Y2.1
unnamed: C43.2, U17.4 (PC15), Y2.3
unnamed: C47.1, U17.30 (VCAP_1)
SWDCLK: J12.9 (TCK/SWCLK), U17.49 (PA14)
SWDIO: J12.7 (TMS/SWDIO), U17.46 (PA13)
